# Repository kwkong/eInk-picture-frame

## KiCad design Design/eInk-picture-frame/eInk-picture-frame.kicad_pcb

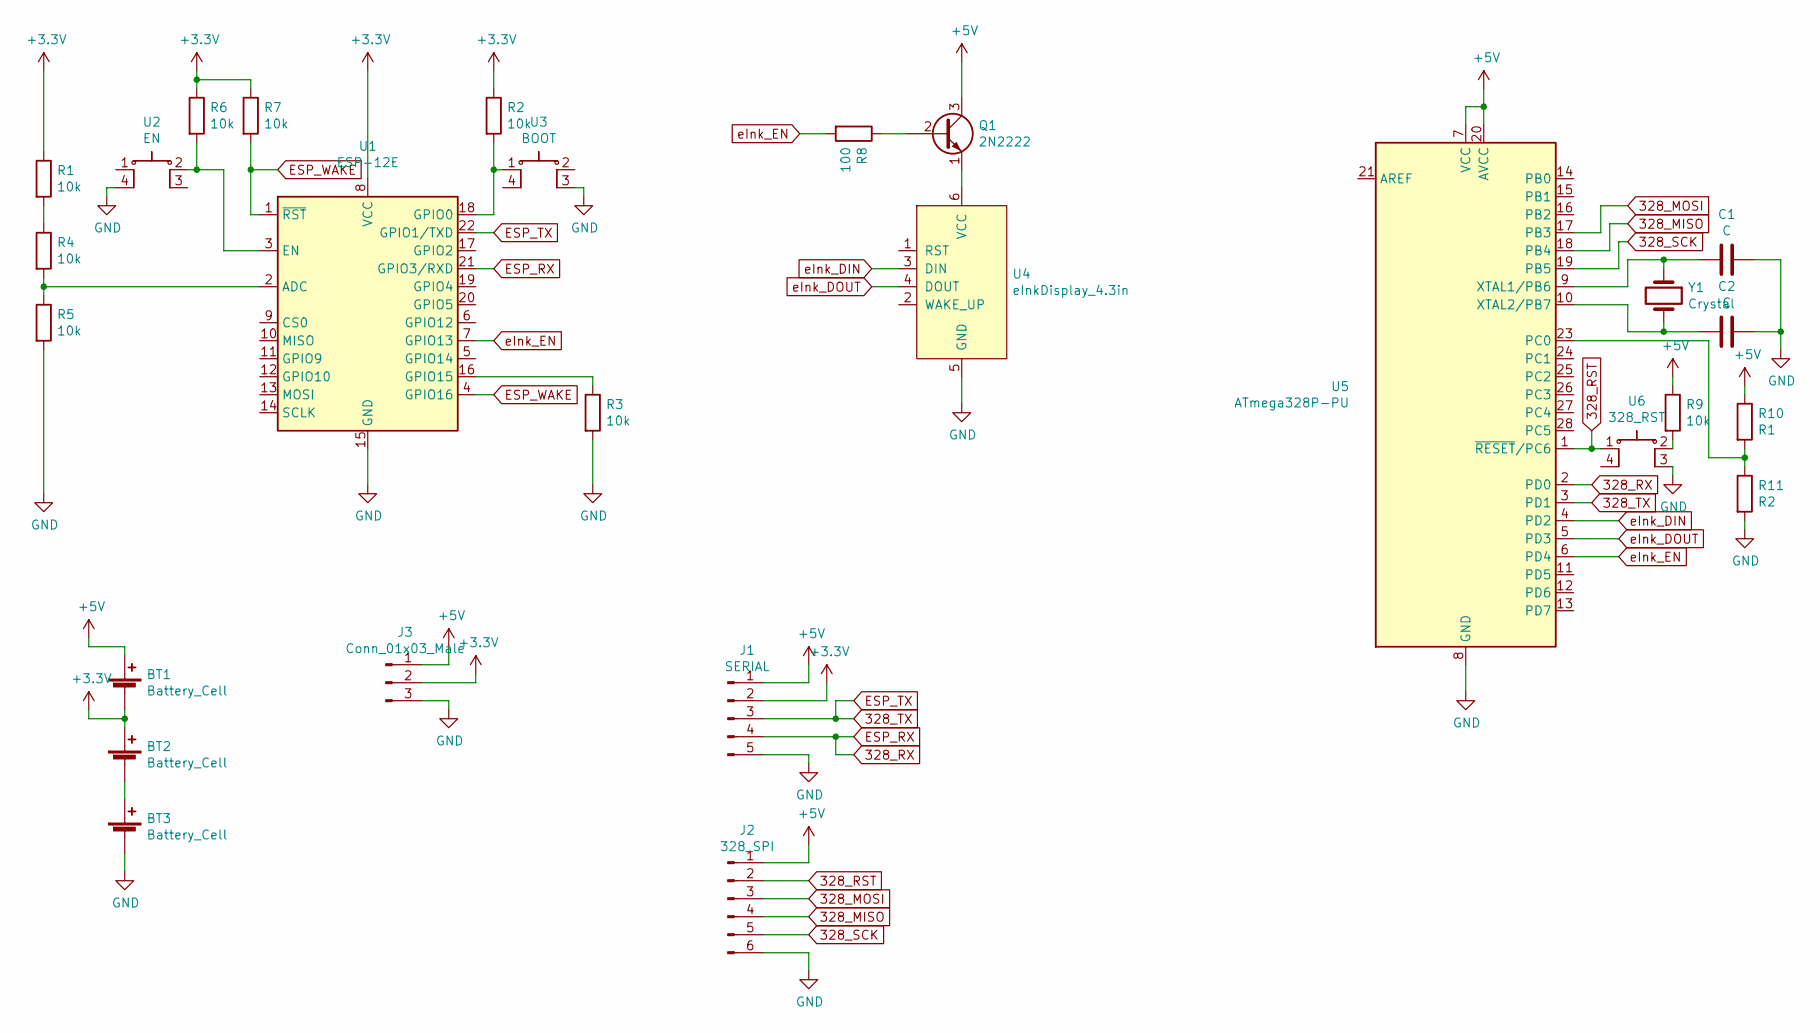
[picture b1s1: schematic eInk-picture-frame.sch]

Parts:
BT1, BT2, BT3: Battery_Cell; BatteryHolder_Keystone_2460_1xAA
C1, C2: C; C_Disc_D3.0mm_W1.6mm_P2.50mm
J1: SERIAL; PinHeader_1x05_P2.54mm_Vertical
J2: 328_SPI; PinHeader_1x06_P2.54mm_Vertical
J3: Conn_01x03_Male; PinHeader_1x03_P2.54mm_Vertical
Q1: 2N2222; TO-92_Inline
R1, R2, R3, R4, R5, R6, R7, R9: 10k; R_Axial_DIN0207_L6.3mm_D2.5mm_P10.16mm_Horizontal
R8: 100; R_Axial_DIN0207_L6.3mm_D2.5mm_P10.16mm_Horizontal
R10: R1; R_Axial_DIN0207_L6.3mm_D2.5mm_P10.16mm_Horizontal
R11: R2; R_Axial_DIN0207_L6.3mm_D2.5mm_P10.16mm_Horizontal
U1: ESP-12E
U2: EN; 6mm_momentary_switch_DIP
U3: BOOT; 6mm_momentary_switch_DIP
U4: eInkDisplay_4.3in; PinHeader_1x06_P2.54mm_Vertical
U5: ATmega328P-PU; DIP-28_W7.62mm
U6: 328_RST; 6mm_momentary_switch_DIP
Y1: Crystal; Crystal_HC18-U_Vertical

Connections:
328_MISO: J2.4, U5.18 (PB4)
328_MOSI: J2.3, U5.17 (PB3)
328_RST: J2.2, U5.1 (~RESET~/PC6), U6.1
328_RX: J1.4, U1.21 (GPIO3/RXD), U5.2 (PD0)
328_SCK: J2.5, U5.19 (PB5)
328_TX: J1.3, U1.22 (GPIO1/TXD), U5.3 (PD1)
+3V3: BT1.2 (-), BT2.1 (+), J1.2, J3.2, R1.1, R2.1, R6.1, R7.1, U1.8 (VCC)
+5V: BT1.1 (+), J1.1, J2.1, J3.1, Q1.3 (C), R9.1, R10.1, U5.7 (VCC), U5.20 (AVCC)
ESP_WAKE: R7.2, U1.1 (~RST), U1.4 (GPIO16)
GND: BT3.2 (-), C1.2, C2.2, J1.5, J2.6, J3.3, R3.2, R5.2, R11.2, U1.15 (GND), U2.4, U3.3, U4.5 (GND), U5.8 (GND), U5.22 (GND), U6.3
unnamed: BT2.2 (-), BT3.1 (+)
unnamed: C1.1, U5.9 (XTAL1/PB6), Y1.1
unnamed: C2.1, U5.10 (XTAL2/PB7), Y1.2
unnamed: Q1.1 (E), U4.6 (VCC)
unnamed: Q1.2 (B), R8.1
unnamed: R1.2, R4.1
unnamed: R2.2, U1.18 (GPIO0), U3.1
unnamed: R3.1, U1.16 (GPIO15)
unnamed: R4.2, R5.1, U1.2 (ADC)
unnamed: R6.2, U1.3 (EN), U2.2
unnamed: R9.2, U6.2
unnamed: R10.2, R11.1, U5.23 (PC0)
eInk_DIN: U4.3 (DIN), U5.4 (PD2)
eInk_DOUT: U4.4 (DOUT), U5.5 (PD3)
eInk_EN: R8.2, U1.7 (GPIO13), U5.6 (PD4)

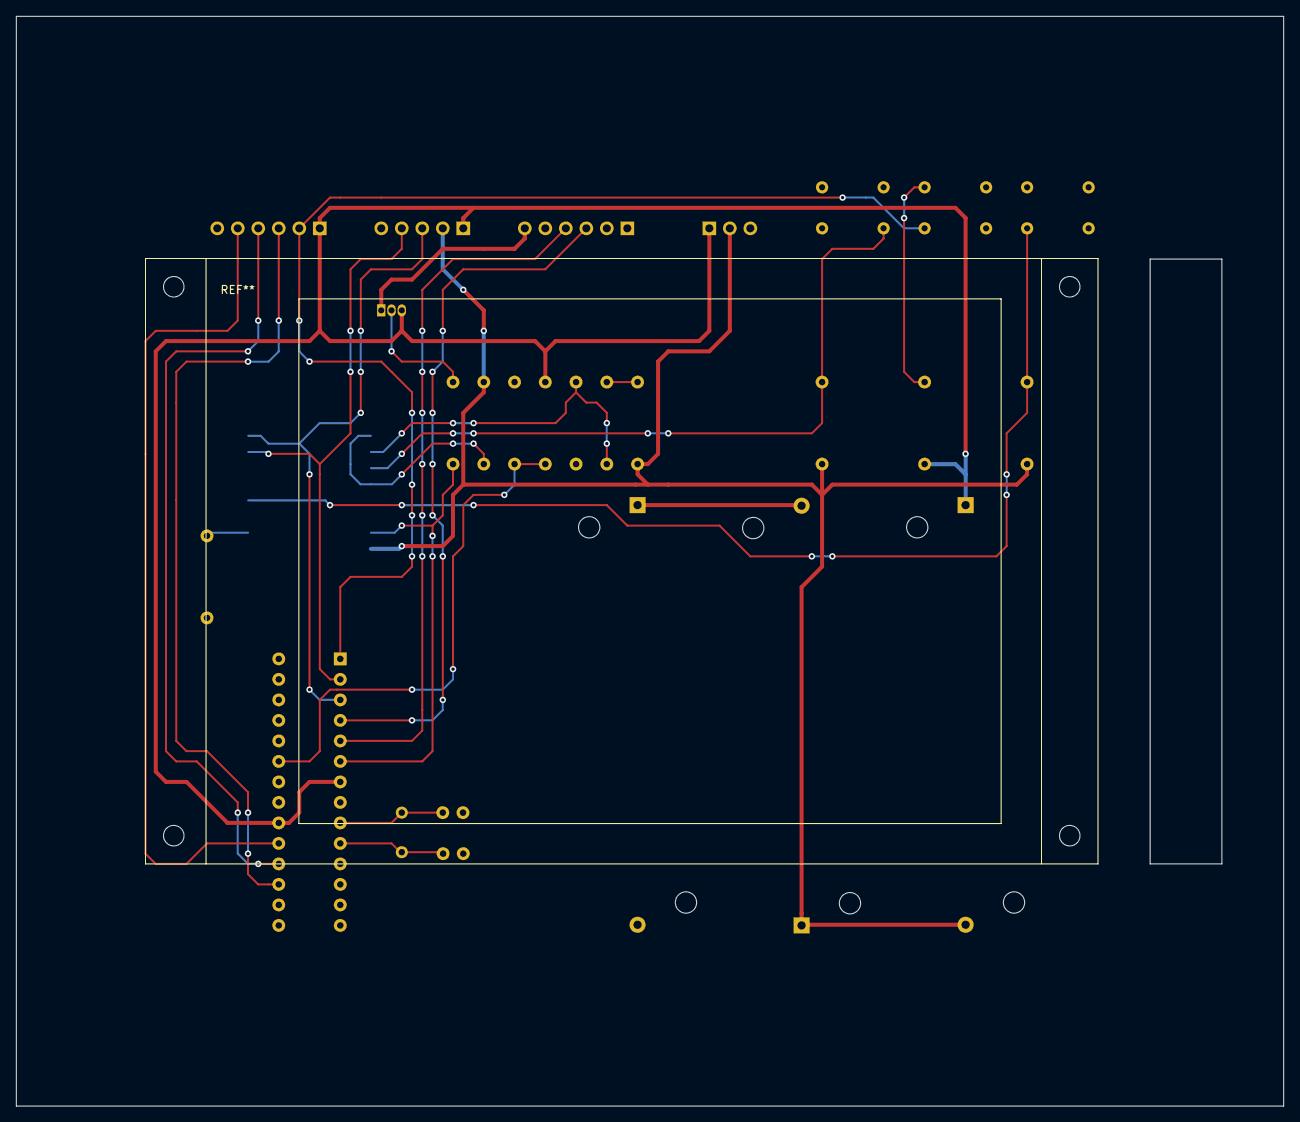
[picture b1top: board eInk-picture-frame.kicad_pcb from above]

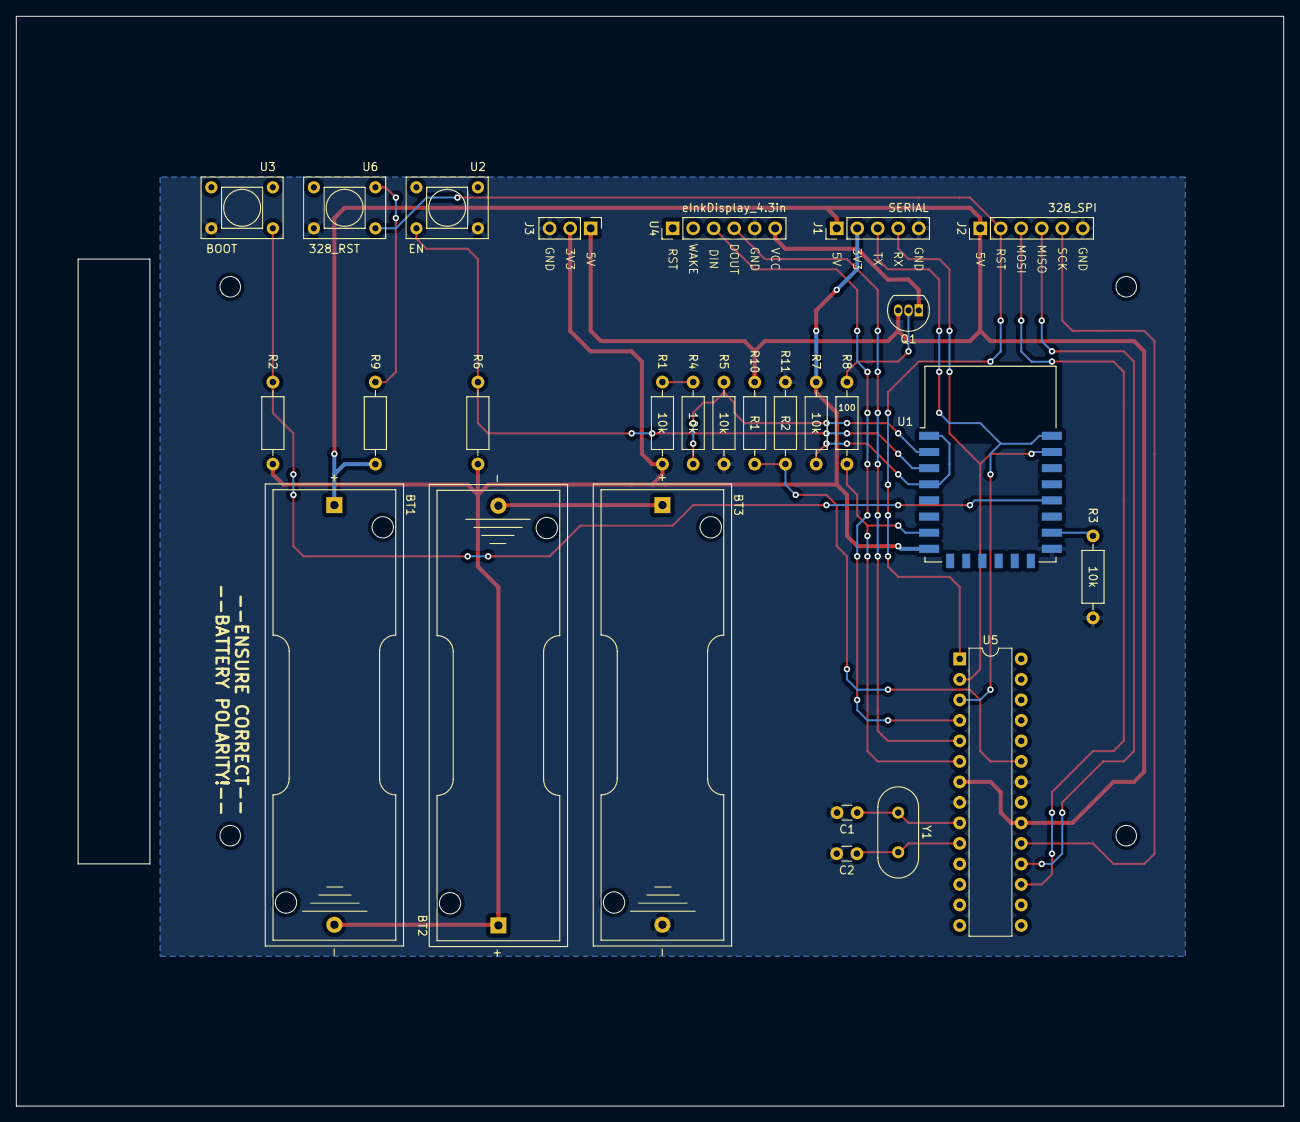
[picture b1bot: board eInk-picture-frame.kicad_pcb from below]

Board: 2 copper layers, 157.0 x 135.0 mm, 27 parts (27 on the bottom side), 25 nets.

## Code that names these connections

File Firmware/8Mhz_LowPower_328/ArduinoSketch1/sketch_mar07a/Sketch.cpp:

#include <Arduino.h>
#include "EEPROM.h"
#include "LowPower.h"
#include "epd.h"

#define imageMaximum 17
#define imageCounterAddress 1
#define eink_EN 4
#define eink_DIN 2
#define eink_DOUT 3

unsigned long dayCounter = 0;
unsigned long holdTimer = 0;

void displayImage();
void restartCounter();

void setup()
{
	//restartCounter();
	pinMode(eink_DIN, INPUT_PULLUP);
	if(!digitalRead(eink_DIN))
	{
		holdTimer = millis();
		while(!digitalRead(eink_DIN));
		
		if((millis() - holdTimer) > 3000)
		{
			int imageCounter = 0;
			EEPROM.put(imageCounterAddress,imageCounter);
		}
	}
	displayImage();
}

void loop()
{
	if(dayCounter > 300000)
	{
		displayImage();
		dayCounter = 0;
	}

	dayCounter++;
	LowPower.powerDown(SLEEP_8S, ADC_OFF, BOD_OFF);
}

void displayImage()
{
    pinMode(eink_EN, OUTPUT);
    digitalWrite(eink_EN, HIGH);
    delay(5000);

    Serial.begin(115200);
    epd_set_memory(MEM_TF);
	
	int imageCounter = 0;
	String imageName = "o";

	
	EEPROM.get(imageCounterAddress, imageCounter);
	imageCounter++;

	if(imageCounter > imageMaximum)
	{
		imageCounter = 0;
	}

	EEPROM.put(imageCounterAddress,imageCounter);

	imageName += String(imageCounter);
	imageName += ".bmp";
	
	
	epd_clear();
	epd_disp_bitmap(imageName.c_str(), 0, 0);
	epd_udpate();
	delay(15000);
	digitalWrite(eink_EN, LOW);
}

void restartCounter()
{
	for (int i = 0 ; i < EEPROM.length() ; i++) 
	{
		EEPROM.write(i, 0);
	}
	
	int imageCounter = 0;
	EEPROM.put(imageCounterAddress, imageCounter);
	//Serial.println("Comment this function out and restart device");
	while(1);
}

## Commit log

2021-03-05 started
2021-03-07 still deciding on esp8266 or atmega328
2021-03-08 version 1 complete
2021-03-21 added epd library
2021-03-23 added pio sketch for debugging
2021-03-24 working demo
    sleep working
    display working
    just need to do battery measuring circuit now
2021-03-29 version 1 code!
